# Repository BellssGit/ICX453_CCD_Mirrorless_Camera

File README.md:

# DIY APS-C Size CCD Sensor Mirrorless Camera

Blog about this project: https://www.emoe.xyz/diy_ccd_camera/ (Chinese)

or https://www.bilibili.com/read/cv41529294/ (Chinese)

## Hardware

1. FPGA Core board --- [Open source ZYNQ7000 Board from oshwhub.com](https://oshwhub.com/z_star/zynq7020-core-board-and-various-rf-modules)
2. CCD Base board --- "CCD_Sensor_ZYNQ_Based_Board" Folder (KiCAD >= 8)
3. Handle and Lens Mount --- "3d_model" Folder (FreeCAD >= 1.0)

## Software

1. "pixel_rearrange.py" for pixel re-arrangement
2. GIMP for gamma correction
3. Fitswork4 for debayer 
4. Photoshop and the "CCD_CameraRAW_Preset" for color grading
5. Vivado 2018.3 and "CCD_Cam_Vivado_workspace.7z" for both PL and PS source code

   Note: Due to Github file size limitation and I dont want to upload the whole workspace folder (because that is a mess), So the workspace is split into two smaller compressed files.

   Update: Just realized I miss a verilog source file "line_skipper.v" which lead to a compile error when generating bitstream. Now the file is in the repo, this is a easy fix. Have fun :)

Some sample photo

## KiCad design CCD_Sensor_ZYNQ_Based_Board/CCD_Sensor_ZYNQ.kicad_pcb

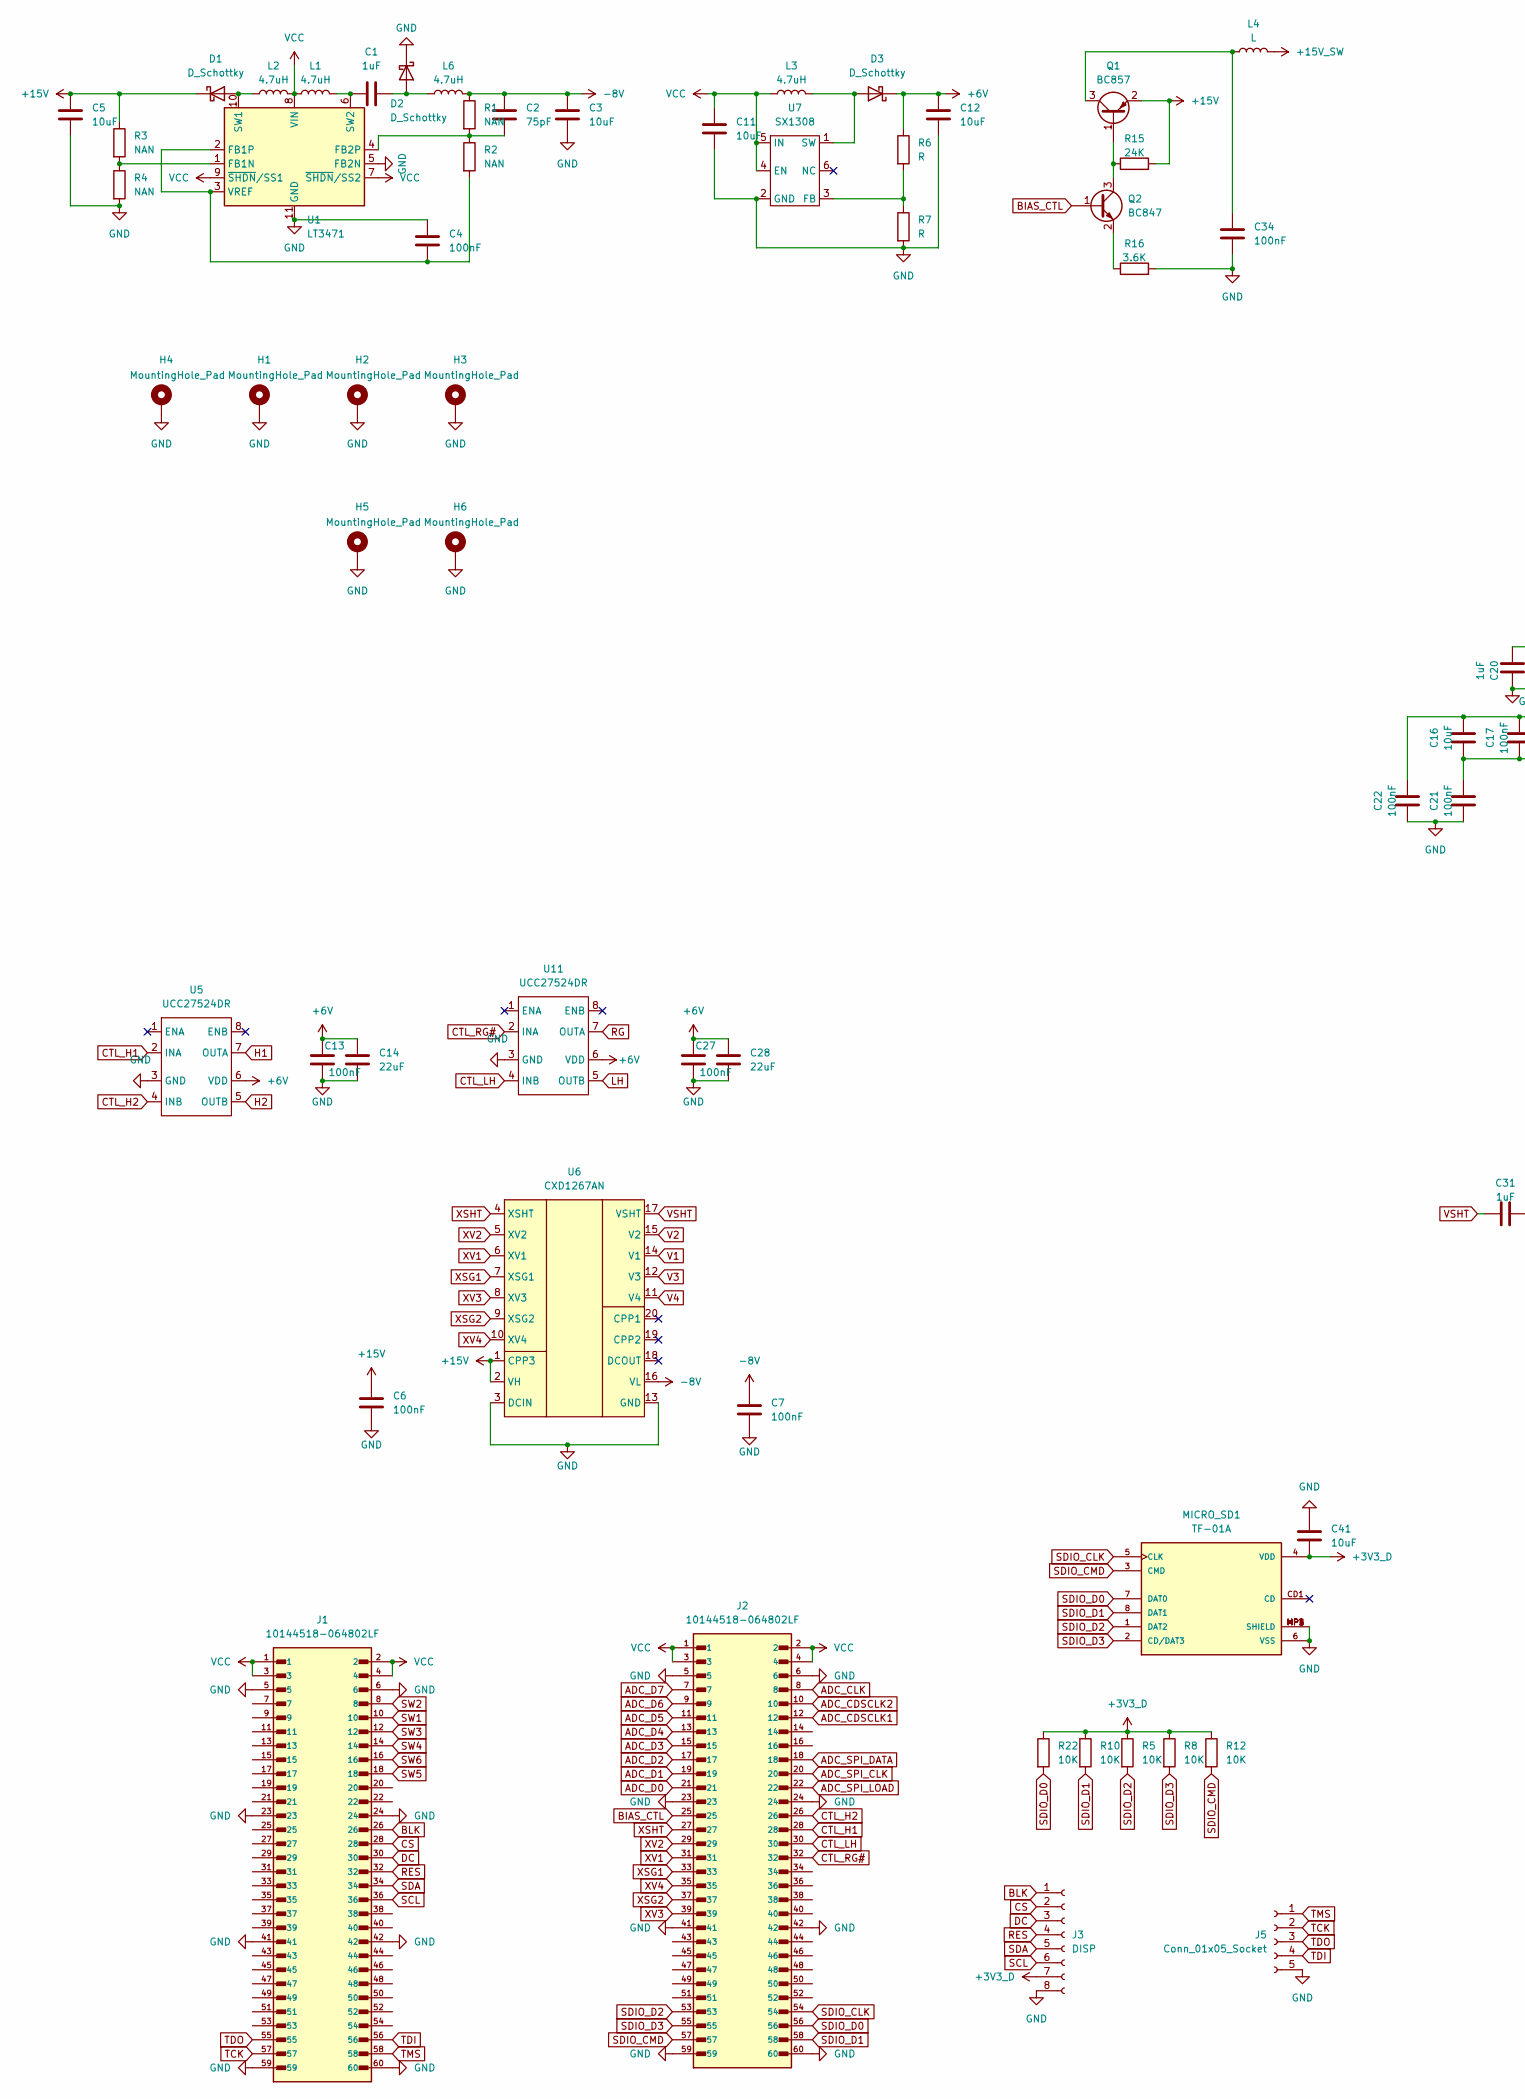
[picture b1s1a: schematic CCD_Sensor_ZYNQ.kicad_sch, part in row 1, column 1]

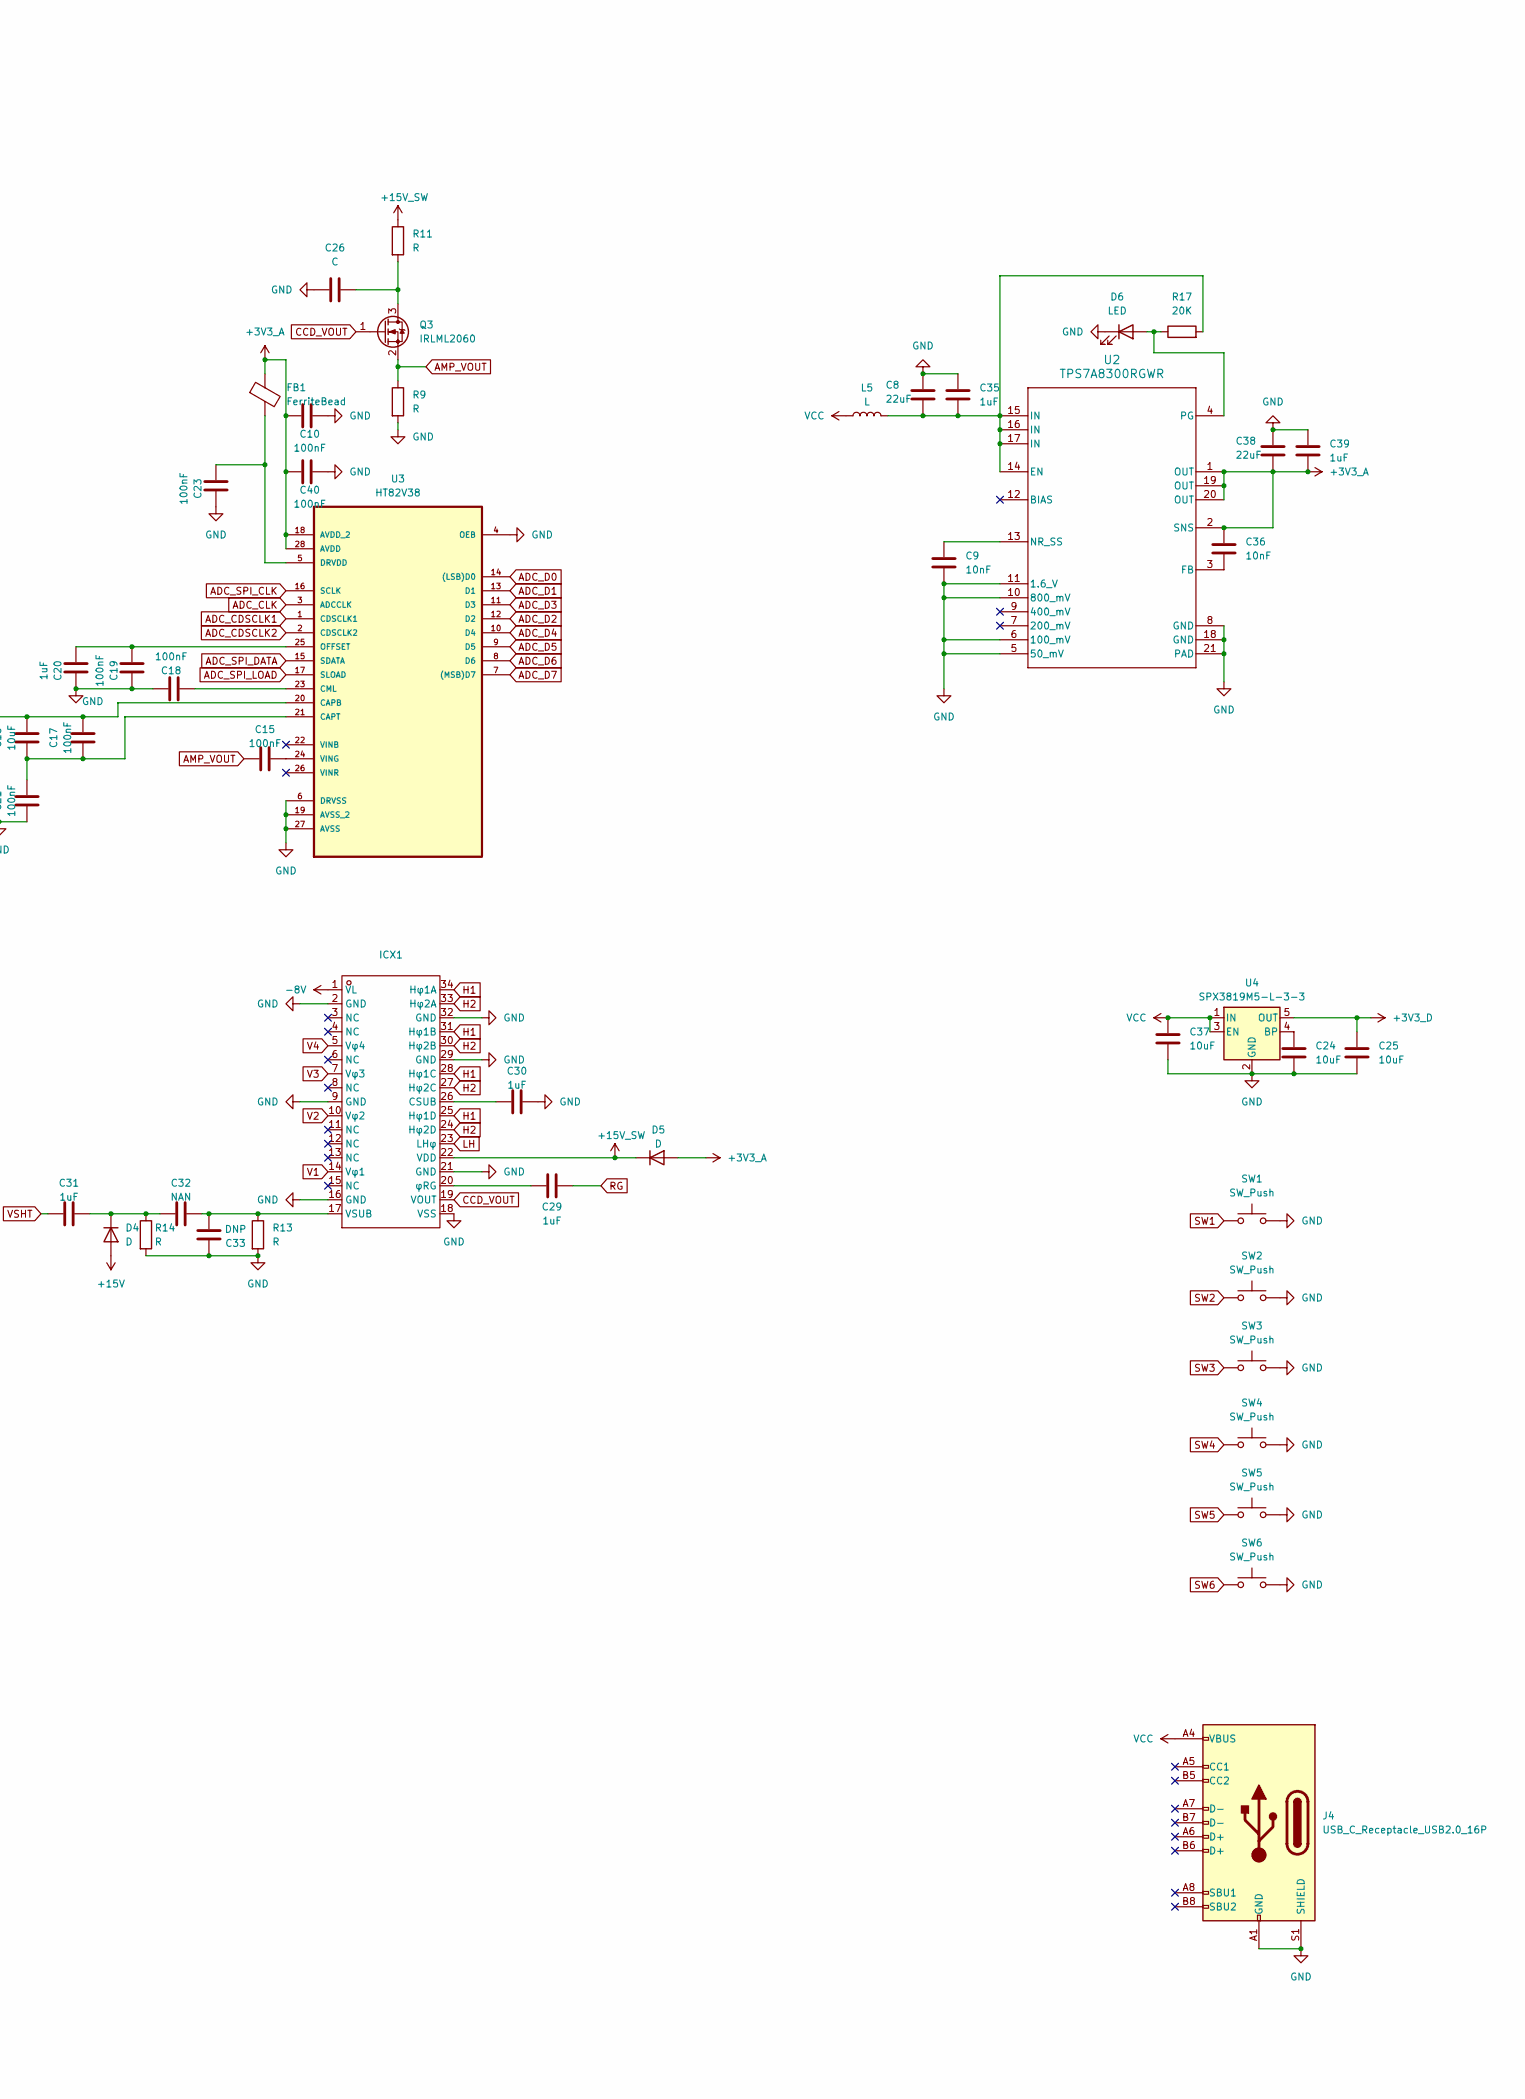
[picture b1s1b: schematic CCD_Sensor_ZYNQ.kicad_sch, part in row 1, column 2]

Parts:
C1: 1uF; C_0603_1608Metric_Pad1.08x0.95mm_HandSolder
C2: 75pF; C_0603_1608Metric_Pad1.08x0.95mm_HandSolder
C3, C5, C12: 10uF; C_0805_2012Metric
C4, C6, C7, C13, C27, C34: 100nF; C_0603_1608Metric_Pad1.08x0.95mm_HandSolder
C8, C38: 22uF; C_0805_2012Metric
C9, C36: 10nF; C_0603_1608Metric
C10, C15, C17, C18, C19, C21, C22, C23, C40: 100nF; C_0603_1608Metric
C11: 10uF; C_0603_1608Metric_Pad1.08x0.95mm_HandSolder
C14, C28: 22uF; C_0805_2012Metric_Pad1.18x1.45mm_HandSolder
C16, C24, C25, C37, C41: 10uF; C_0603_1608Metric
C20, C35, C39: 1uF; C_0603_1608Metric
C26: C; C_0603_1608Metric_Pad1.08x0.95mm_HandSolder
C29, C30, C31: 1uF; C_0805_2012Metric_Pad1.18x1.45mm_HandSolder
C32: NAN; C_0805_2012Metric_Pad1.18x1.45mm_HandSolder
C33: DNP; C_0805_2012Metric_Pad1.18x1.45mm_HandSolder
D1, D2, D3: D_Schottky; D_SOD-123
D4, D5: D; D_SOD-123
D6: LED; LED_0603_1608Metric
FB1: FerriteBead; L_0603_1608Metric
H1, H2, H3, H4, H5, H6: MountingHole_Pad; MountingHole_2.7mm_M2.5_DIN965_Pad
ICX1: DIP-34_1033_ELL
J1, J2: 10144518-064802LF; AMPHENOL_10144518-064802LF; PARTREV H
J3: DISP; PinSocket_1x08_P2.54mm_Vertical
J4: USB_C_Receptacle_USB2.0_16P; USB_C_Receptacle_G-Switch_GT-USB-7010ASV
J5: Conn_01x05_Socket; PinSocket_1x05_P2.54mm_Vertical
L1, L2, L3, L6: 4.7uH; L_Changjiang_FNR252012S
L4: L; L_0603_1608Metric_Pad1.05x0.95mm_HandSolder
L5: L; L_0805_2012Metric
MICRO_SD1: TF-01A
Q1: BC857; SOT-23
Q2: BC847; SOT-23
Q3: IRLML2060; SOT-23
R1, R2, R3, R4: NAN; R_0603_1608Metric
R5, R8, R10, R12, R22: 10K; R_0603_1608Metric
R6, R7, R13, R14: R; R_0603_1608Metric_Pad0.98x0.95mm_HandSolder
R9, R11: R; R_0603_1608Metric
R15: 24K; R_0603_1608Metric_Pad0.98x0.95mm_HandSolder
R16: 3.6K; R_0603_1608Metric_Pad0.98x0.95mm_HandSolder
R17: 20K; R_0603_1608Metric
SW1, SW2, SW3, SW4, SW5, SW6: SW_Push; SW_SPST_PTS645
U1: LT3471; DFN-10-1EP_3x3mm_P0.5mm_EP1.65x2.38mm
U2: TPS7A8300RGWR; RGW0020A
U3: HT82V38; SSOP-28_5.3x10.2mm_P0.65mm; MPN AD9826KRSZ
U4: SPX3819M5-L-3-3; SOT-23-5
U5, U11: UCC27524DR; SOIC-8_3.9x4.9mm_P1.27mm
U6: CXD1267AN; TSSOP-20_4.4x6.5mm_P0.65mm
U7: SX1308; SOT-23-6

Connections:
+3V3_A: C10.1, C36.1, C38.2, C39.2, C40.1, D5.2 (A), FB1.1, U2.1 (OUT), U2.2 (SNS), U2.19 (OUT), U2.20 (OUT), U3.18 (AVDD_2), U3.28 (AVDD)
+3V3_D: C25.1, C41.2, J3.7, MICRO_SD1.4 (VDD), R5.1, R8.1, R10.1, R12.1, R22.1, U4.5 (OUT)
+6V: C12.1, C13.1, C14.1, C27.1, C28.1, D3.1 (K), R6.1, U5.6 (VDD), U11.6 (VDD)
+15V: C5.1, C6.1, D1.1 (K), D4.2 (A), Q1.2 (E), R3.1, R15.2, U6.1 (CPP3), U6.2 (VH)
+15V_SW: D5.1 (K), ICX1.22 (VDD), L4.2, R11.1
-8V: C2.2, C3.1, C7.1, ICX1.1 (VL), L6.2, R1.1, U6.16 (VL)
ADC_CDSCLK1: J2.12, U3.1 (CDSCLK1)
ADC_CDSCLK2: J2.10, U3.2 (CDSCLK2)
ADC_CLK: J2.8, U3.3 (ADCCLK)
ADC_D0: J2.21, U3.14 ((LSB)D0)
ADC_D1: J2.19, U3.13 (D1)
ADC_D2: J2.17, U3.12 (D2)
ADC_D3: J2.15, U3.11 (D3)
ADC_D4: J2.13, U3.10 (D4)
ADC_D5: J2.11, U3.9 (D5)
ADC_D6: J2.9, U3.8 (D6)
ADC_D7: J2.7, U3.7 ((MSB)D7)
ADC_SPI_CLK: J2.20, U3.16 (SCLK)
ADC_SPI_DATA: J2.18, U3.15 (SDATA)
ADC_SPI_LOAD: J2.22, U3.17 (SLOAD)
AMP_VOUT: C15.1, Q3.2 (S), R9.1
BIAS_CTL: J2.25, Q2.1 (B)
BLK: J1.26, J3.1
CCD_VOUT: ICX1.19 (VOUT), Q3.1 (G)
CS: J1.28, J3.2
CTL_H1: J2.28, U5.2 (INA)
CTL_H2: J2.26, U5.4 (INB)
CTL_LH: J2.30, U11.4 (INB)
CTL_RG#: J2.32, U11.2 (INA)
DC: J1.30, J3.3
GND: C3.2, C4.2, C5.2, C6.2, C7.2, C8.1, C9.2, C10.2, C11.2, C12.2, C13.2, C14.2, C18.2, C19.2, C20.2, C21.1, C22.1, C23.2, C24.2, C25.2, C26.1, C27.2, C28.2, C30.2, C33.1, C34.2, C35.1, C37.2, C38.1, C39.1, C40.2, C41.1, D2.1 (K), D6.1 (K), H1.1, H2.1, H3.1, H4.1, H5.1, H6.1, ICX1.2 (GND), ICX1.9 (GND), ICX1.16 (GND), ICX1.18 (VSS), ICX1.21 (GND), ICX1.29 (GND), ICX1.32 (GND), J1.5, J1.6, J1.23, J1.24, J1.41, J1.42, J1.59, J1.60, J2.5, J2.6, J2.23, J2.24, J2.41, J2.42, J2.59, J2.60, J3.8, J4.A1 (GND), J4.A12 (GND), J4.B1 (GND), J4.B12 (GND), J4.S1 (SHIELD), J5.5, MICRO_SD1.6 (VSS), MICRO_SD1.MP1 (SHIELD), MICRO_SD1.MP2 (SHIELD), MICRO_SD1.MP3 (SHIELD), MICRO_SD1.MP4 (SHIELD), R4.2, R7.2, R9.2, R13.2, R14.2, R16.2, SW1.2, SW2.2, SW3.2, SW4.2, SW5.2, SW6.2, U1.5 (FB2N), U1.11 (GND), U2.5 (50_mV), U2.6 (100_mV), U2.8 (GND), U2.10 (800_mV), U2.11 (1.6_V), U2.18 (GND), U2.21 (PAD), U3.4 (OEB), U3.6 (DRVSS), U3.19 (AVSS_2), U3.27 (AVSS), U4.2 (GND), U5.3 (GND), U6.3 (DCIN), U6.13 (GND), U7.2 (GND), U11.3 (GND)
H1: ICX1.25 (Hφ1D), ICX1.28 (Hφ1C), ICX1.31 (Hφ1B), ICX1.34 (Hφ1A), U5.7 (OUTA)
H2: ICX1.24 (Hφ2D), ICX1.27 (Hφ2C), ICX1.30 (Hφ2B), ICX1.33 (Hφ2A), U5.5 (OUTB)
LH: ICX1.23 (LHφ), U11.5 (OUTB)
unnamed: D1.2 (A), L2.1, U1.10 (SW1)
unnamed: C1.2, D2.2 (A), L6.1
unnamed: D3.2 (A), L3.2, U7.1 (SW)
unnamed: C31.2, C32.1, D4.1 (K), R14.1
unnamed: D6.2 (A), R17.1, U2.4 (PG)
unnamed: C30.1, ICX1.26 (CSUB)
unnamed: C32.2, C33.2, ICX1.17 (VSUB), R13.1
unnamed: C29.1, ICX1.20 (φRG)
unnamed: Q1.1 (B), Q2.3 (C), R15.1
unnamed: C34.1, L4.1, Q1.3 (C)
unnamed: Q2.2 (E), R16.1
unnamed: C26.2, Q3.3 (D), R11.2
unnamed: R3.2, R4.1, U1.1 (FB1N)
unnamed: C4.1, R2.2, U1.2 (FB1P), U1.3 (VREF)
unnamed: C2.1, R1.2, R2.1, U1.4 (FB2P)
unnamed: C1.1, L1.2, U1.6 (SW2)
unnamed: C8.2, C35.2, L5.2, R17.2, U2.14 (EN), U2.15 (IN), U2.16 (IN), U2.17 (IN)
unnamed: C36.2, U2.3 (FB)
unnamed: C9.1, U2.13 (NR_SS)
unnamed: C16.2, C17.2, C22.2, U3.20 (CAPB)
unnamed: C16.1, C17.1, C21.2, U3.21 (CAPT)
unnamed: C18.1, U3.23 (CML)
unnamed: C23.1, FB1.2, U3.5 (DRVDD)
unnamed: C19.1, C20.1, U3.25 (OFFSET)
unnamed: C15.2, U3.24 (VING)
unnamed: C24.1, U4.4 (BP)
unnamed: R6.2, R7.1, U7.3 (FB)
RES: J1.32, J3.4
RG: C29.2, U11.7 (OUTA)
SCL: J1.36, J3.6
SDA: J1.34, J3.5
SDIO_CLK: J2.54, MICRO_SD1.5 (CLK)
SDIO_CMD: J2.57, MICRO_SD1.3 (CMD), R12.2
SDIO_D0: J2.56, MICRO_SD1.7 (DAT0), R22.2
SDIO_D1: J2.58, MICRO_SD1.8 (DAT1), R10.2
SDIO_D2: J2.53, MICRO_SD1.1 (DAT2), R5.2
SDIO_D3: J2.55, MICRO_SD1.2 (CD/DAT3), R8.2
SW1: J1.10, SW1.1
SW2: J1.8, SW2.1
SW3: J1.12, SW3.1
SW4: J1.14, SW4.1
SW5: J1.18, SW5.1
SW6: J1.16, SW6.1
TCK: J1.57, J5.2
TDI: J1.56, J5.4
TDO: J1.55, J5.3
TMS: J1.58, J5.1
V1: ICX1.14 (Vφ1), U6.14 (V1)
V2: ICX1.10 (Vφ2), U6.15 (V2)
V3: ICX1.7 (Vφ3), U6.12 (V3)
V4: ICX1.5 (Vφ4), U6.11 (V4)
VCC: C11.1, C37.1, J1.1, J1.2, J1.3, J1.4, J2.1, J2.2, J2.3, J2.4, J4.A4 (VBUS), J4.A9 (VBUS), J4.B4 (VBUS), J4.B9 (VBUS), L1.1, L2.2, L3.1, L5.1, U1.7 (~SHDN/SS2), U1.8 (VIN), U1.9 (~SHDN/SS1), U4.1 (IN), U4.3 (EN), U7.4 (EN), U7.5 (IN)
VSHT: C31.1, U6.17 (VSHT)
XSG1: J2.33, U6.7 (XSG1)
XSG2: J2.37, U6.9 (XSG2)
XSHT: J2.27, U6.4 (XSHT)
XV1: J2.31, U6.6 (XV1)
XV2: J2.29, U6.5 (XV2)
XV3: J2.39, U6.8 (XV3)
XV4: J2.35, U6.10 (XV4)

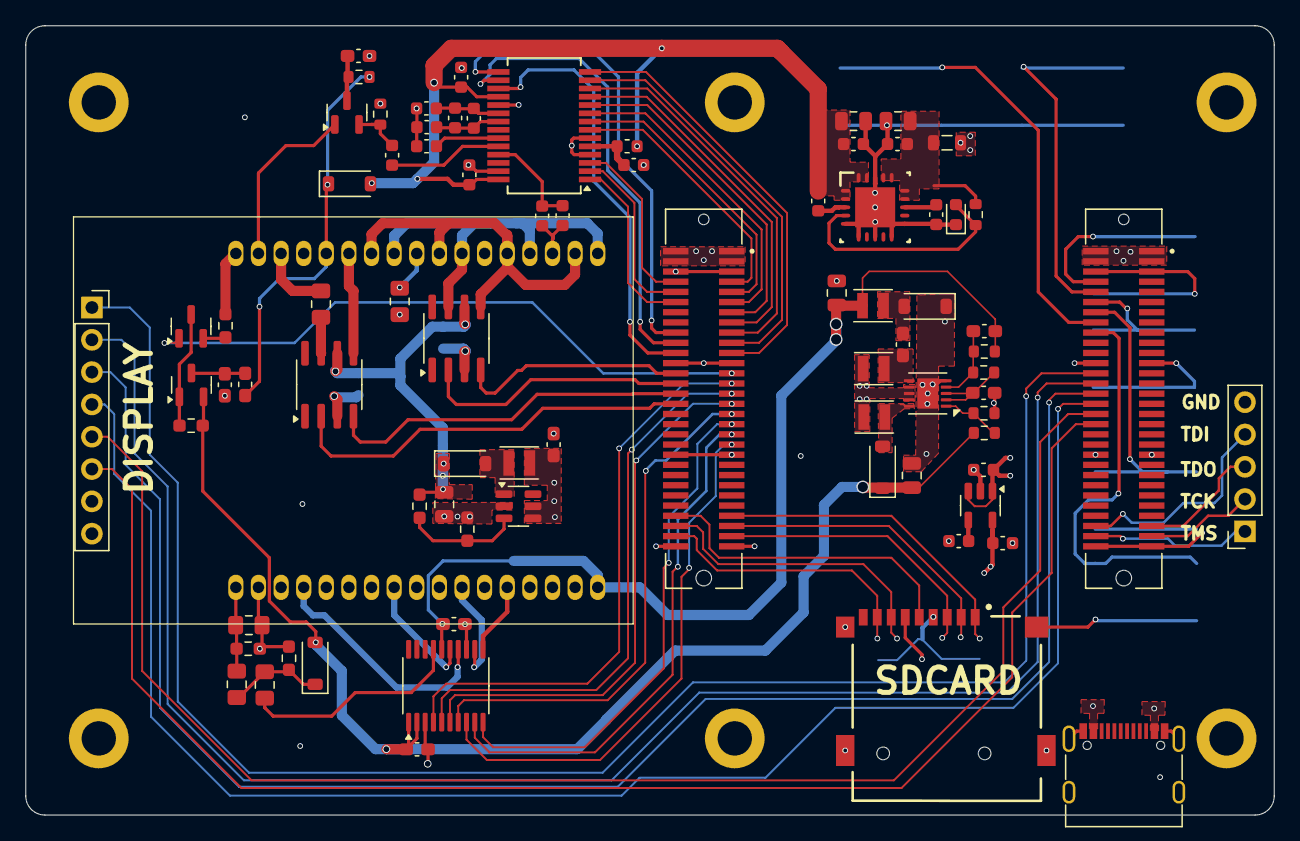
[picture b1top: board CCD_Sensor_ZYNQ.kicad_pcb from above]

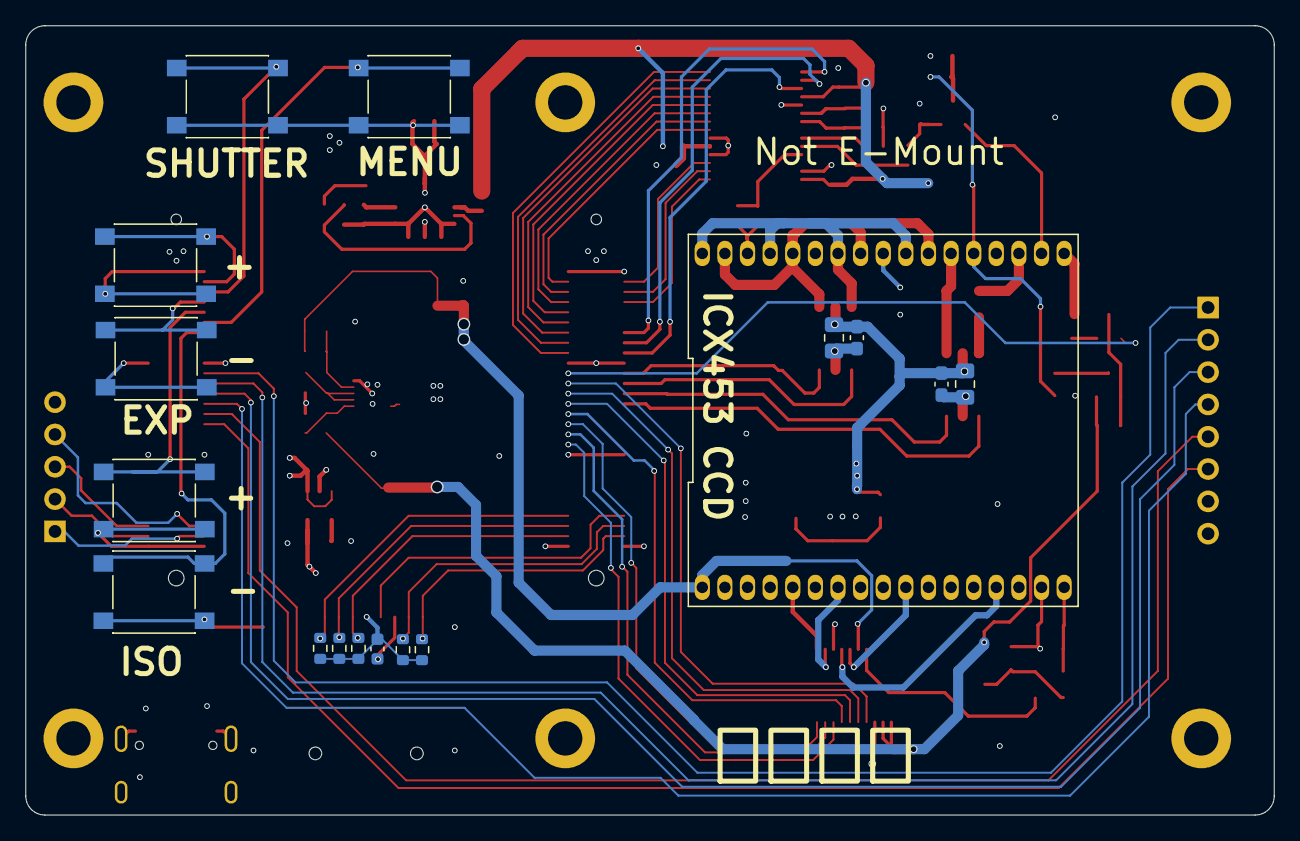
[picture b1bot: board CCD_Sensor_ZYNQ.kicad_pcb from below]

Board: 4 copper layers, 98.1 x 62.1 mm, 102 parts (17 on the bottom side), 94 nets.

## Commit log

2025-05-17 Add missing file "line_skipper.v"
